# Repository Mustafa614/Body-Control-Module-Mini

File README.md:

# Body-Control-Module-Mini
This Module are controlling wipers,baclights,door statues and comminicates with another ecu's via can bus

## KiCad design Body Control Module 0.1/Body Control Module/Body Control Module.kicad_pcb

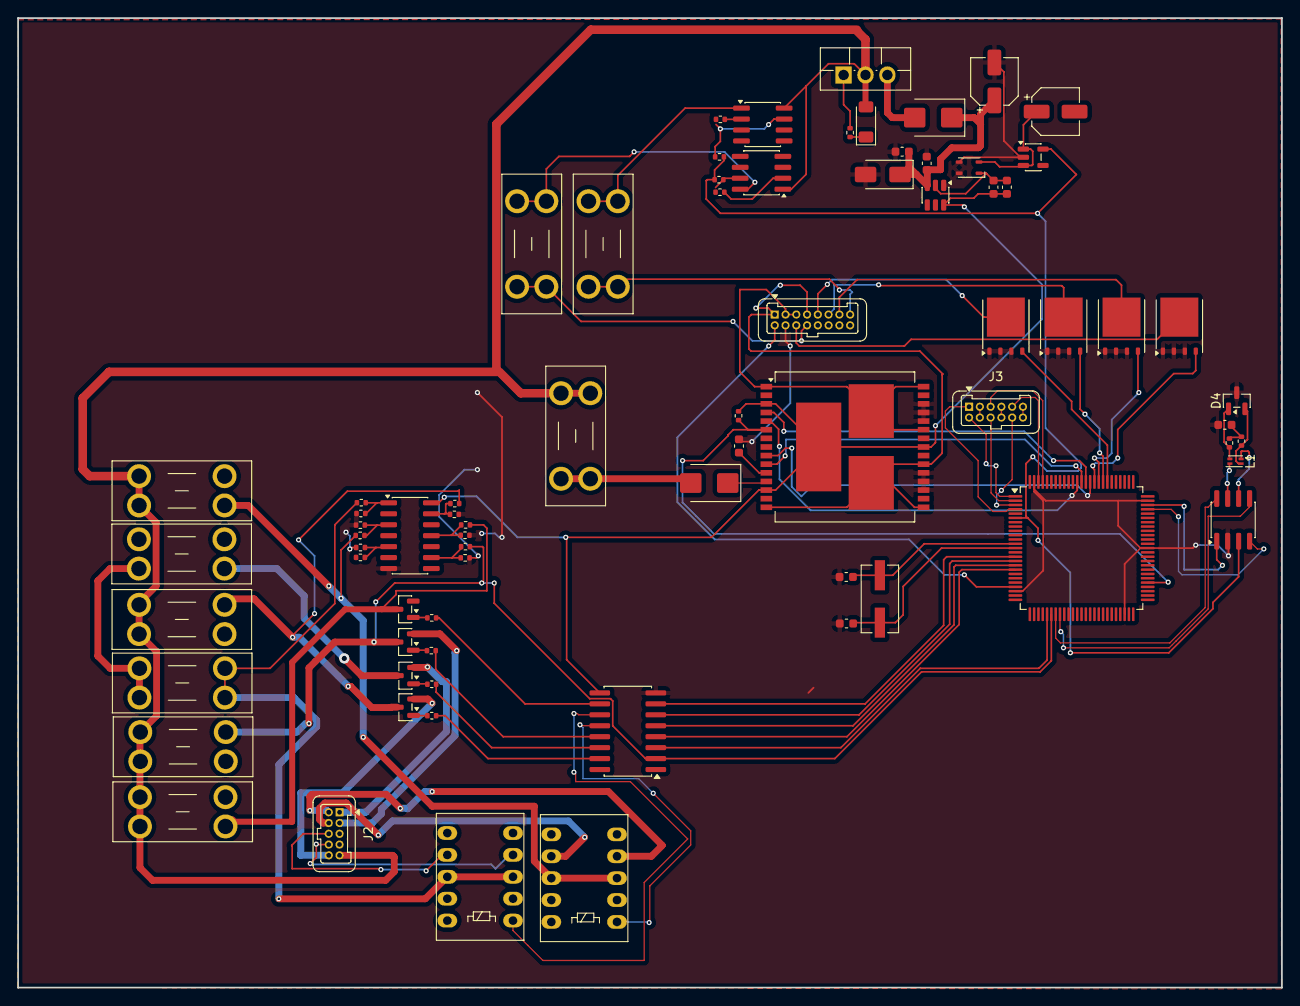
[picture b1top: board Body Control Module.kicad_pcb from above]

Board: 2 copper layers, 146.6 x 112.5 mm, 74 parts (0 on the bottom side), 91 nets.

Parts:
C1: C22uF; C_0603_1608Metric
C1.2, C1.4, C1.5: C10nf; C_0603_1608Metric
C2, C6: C_47uF; CP_Elec_5x3
C3, C5: C0.1uF; C_0603_1608Metric
C4, C7: C22uf; C_0603_1608Metric
D1: BZV55C15; D_MiniMELF
D1.1, D2: SM6T30A; D_SMB
D3: SMAJ18CA; D_SMA
D4: SZNUP2105L; SOT-23
F0.1, F0.2, F1, F1.1, F2, F3, F4, F5, F6: Fuse; Fuseholder_Blade_Mini_Keystone_3568
J1: Conn_02x08_Counter_Clockwise; Harwin_Gecko-G125-FVX1605L0X_2x08_P1.25mm_Vertical
J2: Conn_02x05_Counter_Clockwise; Harwin_Gecko-G125-FVX1005L0X_2x05_P1.25mm_Vertical
J3: Conn_02x06_Counter_Clockwise; Harwin_Gecko-G125-FVX1205L0X_2x06_P1.25mm_Vertical
K1, K2: AZ850P1-x; Relay_DPDT_FRT5
L1: L_Coupled; L_CommonModeChoke_Coilcraft_0603USB
L2: L_Ferrite_Coupled; L_CommonModeChoke_TDK_ACM2520-2P
Q0.1, Q0.2, Q0.3, Q0.4: BSC340N08NS3G; TDSON-8-1
Q1: IRF4905; TO-220F-3_Vertical
Q2, Q3, Q4, Q5: Si2371EDS; SOT-23
R0.1, R0.2, R0.3, R0.4, R0.5: 10K; R_0402_1005Metric
R1, R2, R3, R4, R5, R6, R7, R8, R9, R10, R11, R12, R14, R16, R17, R18: 100R; R_0402_1005Metric
R13: R100K; R_0402_1005Metric
R19: 60R; R_0402_1005Metric
R20: 60r; R_0402_1005Metric
U0.1, U0.2: AD8418; SOIC-8_3.9x4.9mm_P1.27mm
U1: STM32G431VBTx; LQFP-100_14x14mm_P0.5mm
U1.1: VNH5019A-E; ST_MultiPowerSO-30
U2: SN74LS07N; SOIC-14_3.9x8.7mm_P1.27mm
U3: TPS54202DDC; SOT-23-6
U4: TJA1051T-E; SOIC-8_3.9x4.9mm_P1.27mm
U5: MIC5504-3.3YM5; SOT-23-5
U6: ULN2003A; SOIC-16W_5.3x10.2mm_P1.27mm
Y1: Crystal; Crystal_SMD_ECS_CSM3X-2Pin_7.6x4.1mm

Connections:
+3.3V: R0.3.2, R0.4.2, U1.6 (VBAT), U4.3 (VCC), U5.5 (VOUT)
+3.3VA: J3.2, J3.4, J3.6, J3.8, J3.10, J3.12
+5V: C4.1, C5.1, R0.1.2, U1.1.3 (VCC), U1.1.13 (VCC), U1.1.23 (VCC), U1.1.31 (VCC), U2.14 (VCC), U3.6 (BOOT), U6.9 (COM)
+12V: D1.2 (A), F1.2, F1.1.1, F2.1, F5.2, F6.1, J2.5, Q1.2 (D), U0.1.8 (IN+), U0.2.1 (IN-)
/A0: J2.6, K1.4
/A1: J2.7, K1.7
/A2: J2.8, K2.7
/A3: J2.9, K2.4
/A4: J2.10, Q2.2 (S)
/A5: J2.1, Q3.2 (S)
/A6: J2.2, Q5.2 (S)
/A14: U1.73 (PA12), U4.1 (TXD)
/A15: U1.72 (PA11), U4.4 (RXD)
/A16: U1.32 (PB0), U4.8 (S)
/A17: U1.33 (PB1), U4.5 (EN)
/A30: U1.15 (PC0), U6.7 (I7)
/A31: U1.16 (PC1), U6.6 (I6)
/A32: U1.17 (PC2), U6.5 (I5)
/A33: U1.18 (PC3), U6.4 (I4)
/A34: U1.30 (PC4), U6.3 (I3)
/A35: F5.1, Q5.3 (D), R6.1, U1.31 (PC5), U6.2 (I2)
/A37: F1.1, Q2.3 (D), R12.2
/A38: F6.2, Q4.3 (D), R11.1
/A39: F4.2, K2.3, K2.8, R2.1
/A40: F2.2, K1.3, K1.8, R1.2
/A50: J3.3, U1.97 (PE0)
/A51: J3.5, U1.98 (PE1)
/A52: J3.7, U1.1 (PE2)
/A53: J3.9, U1.2 (PE3)
/A54: J3.11, U1.3 (PE4)
/A55: J3.1, U1.4 (PE5)
/A60: Q0.1.4 (G), U1.82 (PD0)
/A61: Q0.2.4 (G), U1.83 (PD1)
/A62: Q0.3.4 (G), U1.84 (PD2)
/A63: Q0.4.4 (G), U1.85 (PD3)
/A64: J1.11, Q0.4.5 (D)
/A65: J1.7, Q0.3.5 (D)
/A66: J1.6, Q0.2.5 (D)
/A67: J1.5, Q0.1.5 (D)
/A68: F0.1.2, J1.8
/A69: F0.2.2, J1.12
/A70: J1.9, U1.22 (PA2)
/A85: U1.87 (PD5), U1.1.4 (INA)
/A86: U1.88 (PD6), U1.1.10 (INB)
/A87: R0.1.1, U1.55 (PD8), U1.1.6 (CS_DIS)
/A88: U1.86 (PD4), U1.1.9 (EN/DIAGB)
/A89: U1.89 (PD7), U1.1.5 (EN/DIAGA)
/A90: J1.1, J1.4, U1.1.15 (OUTB), U1.1.16 (OUTB), U1.1.21 (OUTB), U1.1.32 (OUTB)
/A91: J1.2, J1.3, U1.1.1 (OUTA), U1.1.25 (OUTA), U1.1.30 (OUTA), U1.1.33 (OUTA)
GND: C1.2, C1.2.2, C1.4.1, C1.5.2, C2.2, C3.2, C7.2, D3.2 (A2), D4.3 (A), J1.10, J2.3, L2.3, L2.4, Q0.1.1 (S), Q0.1.2 (S), Q0.1.3 (S), Q0.2.1 (S), Q0.2.2 (S), Q0.2.3 (S), Q0.3.1 (S), Q0.3.2 (S), Q0.3.3 (S), Q0.4.1 (S), Q0.4.2 (S), Q0.4.3 (S), R3.1, R4.2, R5.2, R8.2, R9.2, R10.1, U1.23 (VSS), U1.48 (VSS), U1.63 (VSS), U1.74 (VSS), U1.99 (VSS), U1.1.18 (GNDB), U1.1.19 (GNDB), U1.1.20 (GNDB), U1.1.26 (GNDA), U1.1.27 (GNDA), U1.1.28 (GNDA), U2.7 (GND), U3.1 (GND), U4.2 (GND), U5.2 (GND), U6.8 (GND)
GND1: C6.2, K1.10, K2.10
unnamed: C7.1, R19.2, R20.2
unnamed: D1.1 (K), R13.2
unnamed: D1.1.1 (A1), U1.1.12 (VBAT)
unnamed: D1.1.2 (A2), F1.1.2
unnamed: C1.1, C2.1, C3.1, D2.1 (A1), D3.1 (A1), U3.3 (VIN)
unnamed: D2.2 (A2), Q1.3 (S)
unnamed: D4.1 (K), L1.4, R20.1
unnamed: D4.2 (K), L1.2, R19.1
unnamed: F3.2, F4.1
unnamed: Q1.1 (G), R13.1
unnamed: Q2.1 (G), R14.2
unnamed: F3.1, Q3.3 (D)
unnamed: Q3.1 (G), R16.2
unnamed: Q4.1 (G), R18.1
unnamed: Q5.1 (G), R17.2
unnamed: R1.1, R3.2, U2.3
unnamed: R2.2, R4.1, U2.1
unnamed: R5.1, R7.2, U2.5
unnamed: R6.2, R8.1, U2.9
unnamed: R10.2, R12.1, U2.13
unnamed: R9.1, R11.2, U2.11
unnamed: R0.2.2, U0.1.2 (GND)
unnamed: F0.1.1, U0.1.1 (IN-)
unnamed: R0.2.1, R0.3.1, U0.1.7 (REF1)
unnamed: R0.5.2, U0.2.2 (GND)
unnamed: F0.2.1, U0.2.8 (IN+)
unnamed: R0.4.1, R0.5.1, U0.2.7 (REF1)
unnamed: C1.2.1, U1.12 (PF0), Y1.2
unnamed: C1.4.2, U1.13 (PF1), Y1.1
unnamed: C1.5.1, U1.1.11 (CP)
unnamed: C4.2, C5.2, L2.1, U3.2 (SW)
unnamed: L1.1, U4.7 (CANH)
unnamed: L1.3, U4.6 (CANL)
unnamed: C6.1, L2.2, U5.1 (VIN), U5.3 (EN)
unnamed: R14.1, U6.15 (O2)
unnamed: R16.1, U6.14 (O3)
unnamed: R17.1, U6.13 (O4)
unnamed: K1.1, U6.12 (O5)
unnamed: K2.1, U6.11 (O6)
unnamed: R18.2, U6.10 (O7)

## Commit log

2026-01-15 Body Control Module 0.1 version
